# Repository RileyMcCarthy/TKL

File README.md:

# TKL
Custom 10 keyless keyboard PCB and case.

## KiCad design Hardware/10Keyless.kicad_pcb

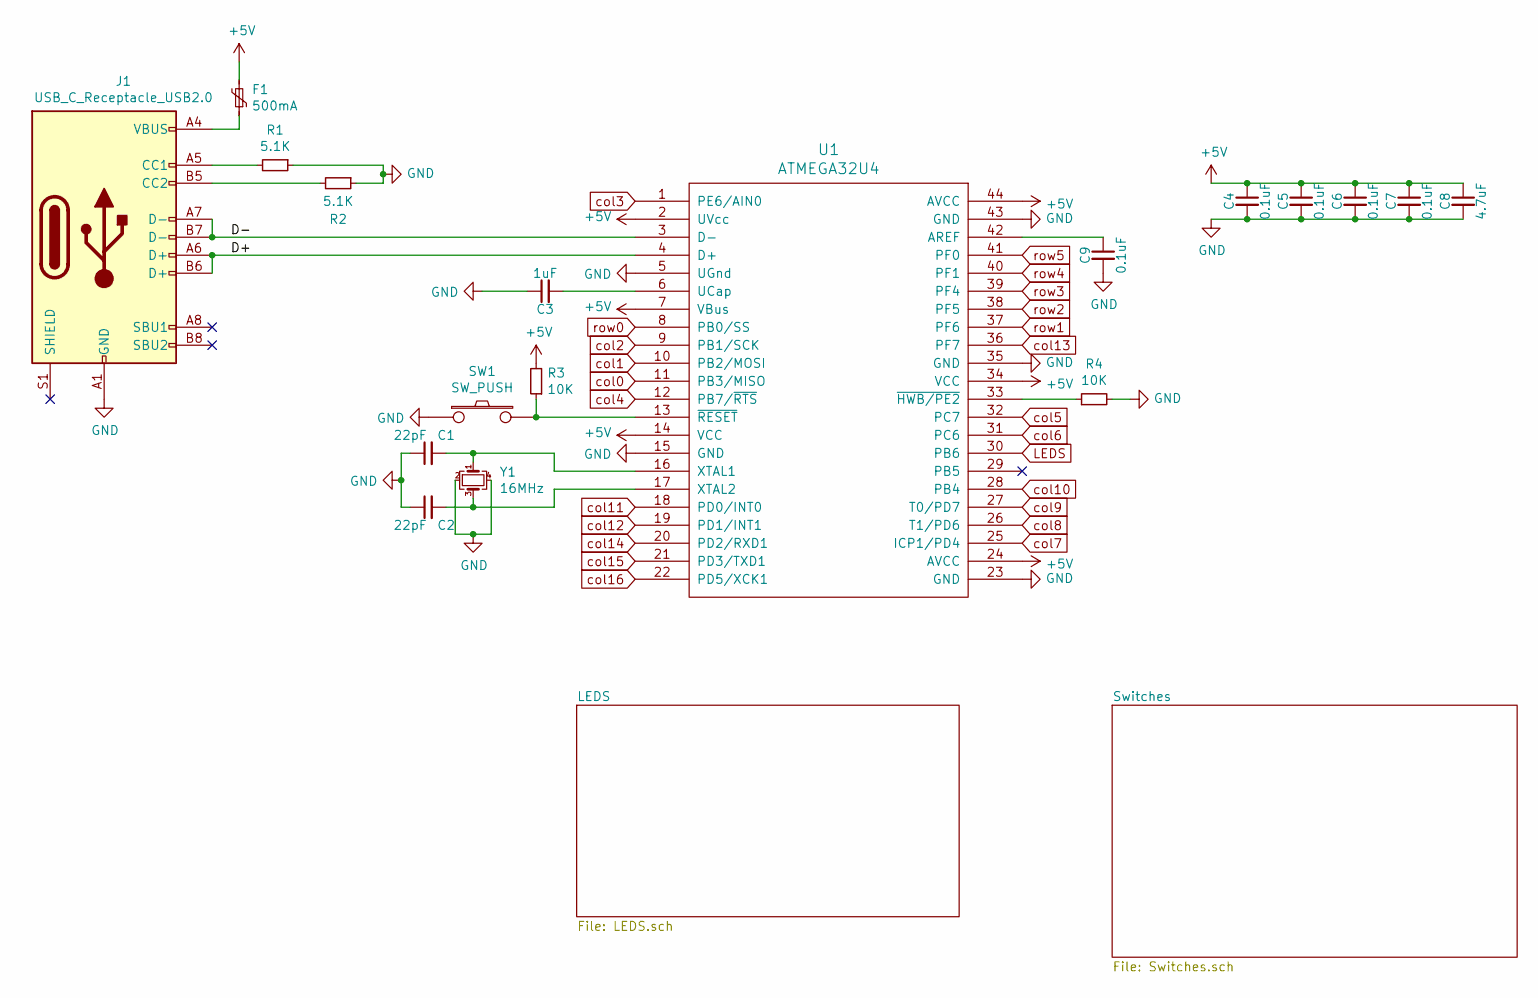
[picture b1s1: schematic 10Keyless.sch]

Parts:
C1, C2: 22pF; C_0603_1608Metric_Pad1.08x0.95mm_HandSolder; LCSC C1653
C3: 1uF; C_0603_1608Metric_Pad1.08x0.95mm_HandSolder; LCSC C15849
C4, C5, C6, C7, C9: 0.1uF; C_0603_1608Metric_Pad1.08x0.95mm_HandSolder; LCSC C14663
C8: 4.7uF; C_0603_1608Metric_Pad1.08x0.95mm_HandSolder; LCSC C19666
F1: 500mA; Fuse_0603_1608Metric_Pad1.05x0.95mm_HandSolder
J1: USB_C_Receptacle_USB2.0; USB_C_Receptacle_Palconn_UTC16-G; LCSC C223907
R1, R2: 5.1K; R_0603_1608Metric; LCSC C23186
R3, R4: 10K; R_0603_1608Metric; LCSC C25804
SW1: SW_PUSH; SW_Push_1P1T_NO_6x6mm_H9.5mm
U1: ATMEGA32U4; LQFP-44_10x10mm_P0.8mm; LCSC C44854
Y1: 16MHz; Crystal_SMD_3225-4Pin_3.2x2.5mm_HandSoldering; LCSC C389842

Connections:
+5V: C4.1, C5.1, C6.1, C7.1, C8.1, F1.2, R3.2, U1.2 (UVcc), U1.7 (VBus), U1.14 (VCC), U1.24 (AVCC), U1.34 (VCC), U1.44 (AVCC); also elsewhere on the board
/D+: J1.A6 (D+), J1.B6 (D+), U1.4 (D+)
/D-: J1.A7 (D-), J1.B7 (D-), U1.3 (D-)
GND: C1.1, C2.1, C3.1, C4.2, C5.2, C6.2, C7.2, C8.2, C9.2, J1.A1 (GND), J1.A12 (GND), J1.B1 (GND), J1.B12 (GND), R1.1, R2.1, R4.2, SW1.1, U1.5 (UGnd), U1.15 (GND), U1.23 (GND), U1.35 (GND), U1.43 (GND), Y1.2, Y1.4; also elsewhere on the board
LEDS: U1.30 (PB6); also elsewhere on the board
unnamed: C1.2, U1.16 (XTAL1), Y1.1
unnamed: C2.2, U1.17 (XTAL2), Y1.3
unnamed: C3.2, U1.6 (UCap)
unnamed: C9.1, U1.42 (AREF)
unnamed: F1.1, J1.A4 (VBUS), J1.A9 (VBUS), J1.B4 (VBUS), J1.B9 (VBUS)
unnamed: J1.A5 (CC1), R1.2
unnamed: J1.B5 (CC2), R2.2
unnamed: R3.1, SW1.2, U1.13 (~RESET)
unnamed: R4.1, U1.33 (~HWB/PE2)
col0: U1.11 (PB3/MISO); also elsewhere on the board
col1: U1.10 (PB2/MOSI); also elsewhere on the board
col2: U1.9 (PB1/SCK); also elsewhere on the board
col3: U1.1 (PE6/AIN0); also elsewhere on the board
col4: U1.12 (PB7/~RTS); also elsewhere on the board
col5: U1.32 (PC7); also elsewhere on the board
col6: U1.31 (PC6); also elsewhere on the board
col7: U1.25 (ICP1/PD4); also elsewhere on the board
col8: U1.26 (T1/PD6); also elsewhere on the board
col9: U1.27 (T0/PD7); also elsewhere on the board
col10: U1.28 (PB4); also elsewhere on the board
col11: U1.18 (PD0/INT0); also elsewhere on the board
col12: U1.19 (PD1/INT1); also elsewhere on the board
col13: U1.36 (PF7); also elsewhere on the board
col14: U1.20 (PD2/RXD1); also elsewhere on the board
col15: U1.21 (PD3/TXD1); also elsewhere on the board
col16: U1.22 (PD5/XCK1); also elsewhere on the board
row0: U1.8 (PB0/SS); also elsewhere on the board
row1: U1.37 (PF6); also elsewhere on the board
row2: U1.38 (PF5); also elsewhere on the board
row3: U1.39 (PF4); also elsewhere on the board
row4: U1.40 (PF1); also elsewhere on the board
row5: U1.41 (PF0); also elsewhere on the board

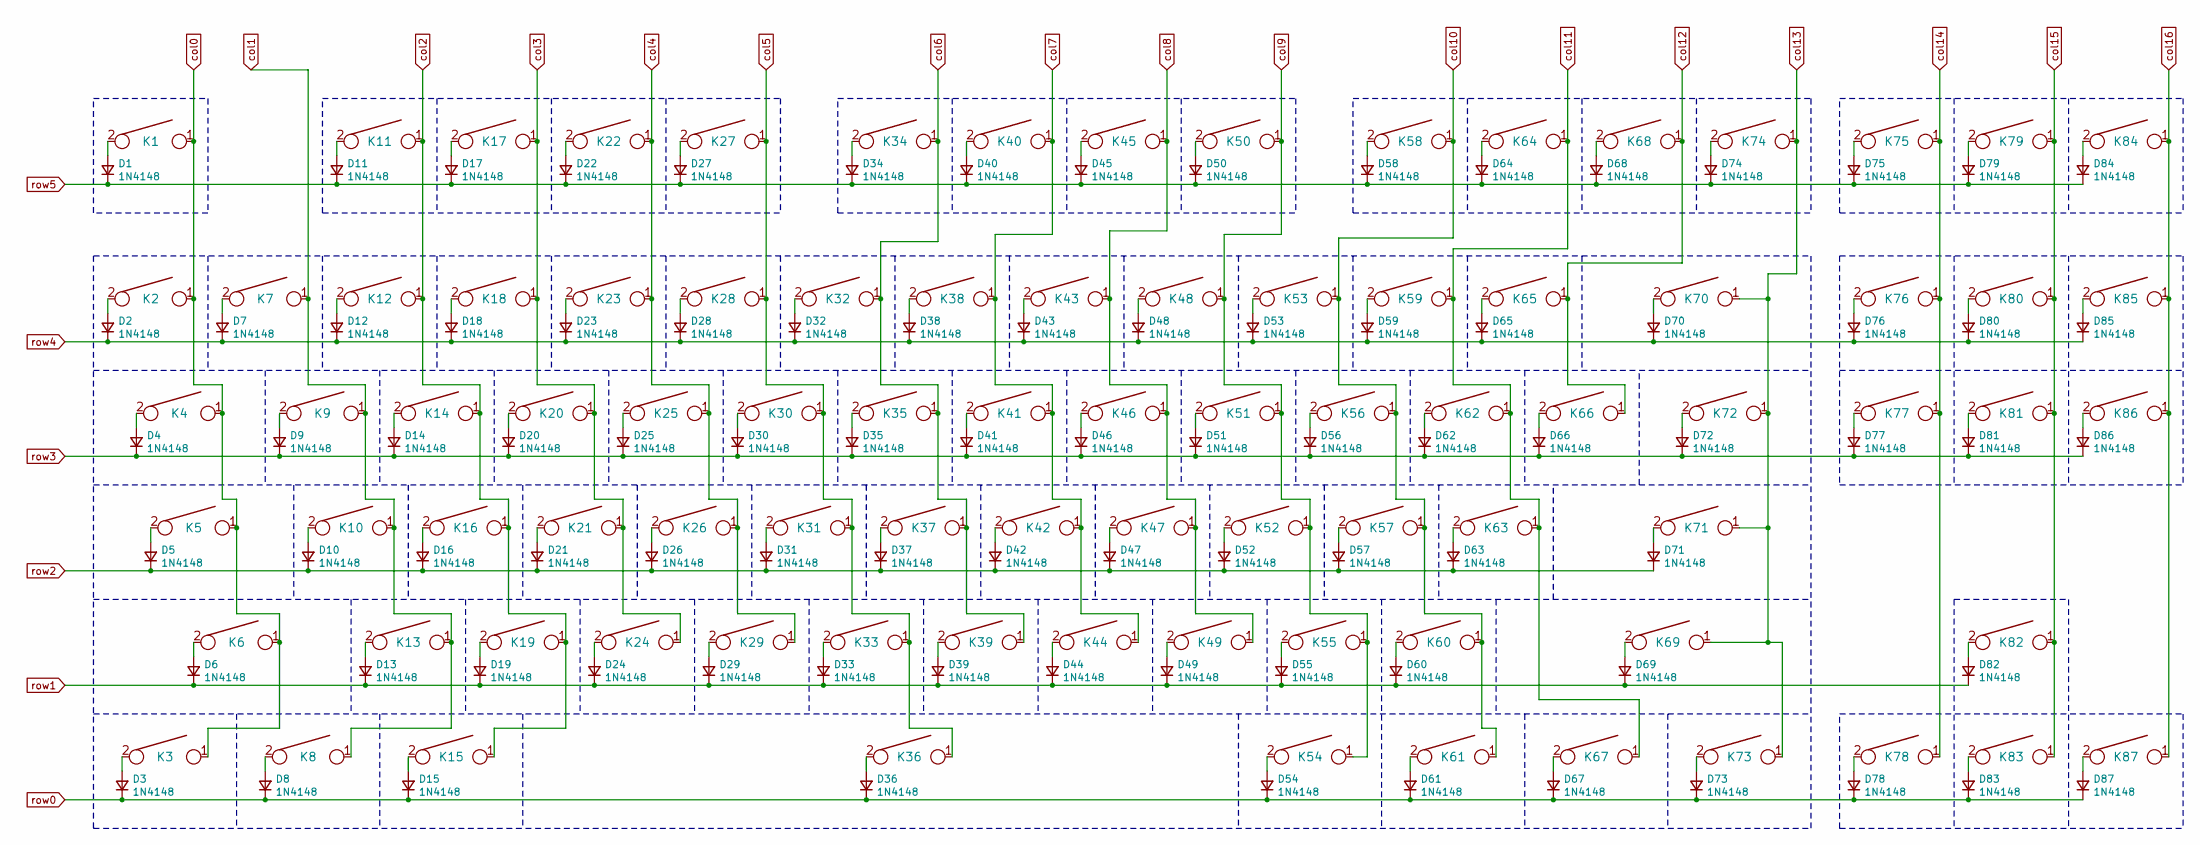
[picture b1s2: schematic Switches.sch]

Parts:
D1, D2, D3, D4, D5, D6, D7, D8, D9, D10, D11, D12, D13, D14, D15, D16, D17, D18, D19, D20, D21, D22, D23, D24, D25, D26, D27, D28, D29, D30, D31, D32, D33, D34, D35, D36, D37, D38, D39, D40, D41, D42, D43, D44, D45, D46, D47, D48, D49, D50, D51, D52, D53, D54, D55, D56, D57, D58, D59, D60, D61, D62, D63, D64, D65, D66, D67, D68, D69, D70, D71, D72, D73, D74, D75, D76, D77, D78, D79, D80, D81, D82, D83, D84, D85, D86, D87: 1N4148; D_SOD-123; LCSC C81598
K1: ESC; SW_Cherry_MX_1.00u_PCB
K2: tilda; SW_Cherry_MX_1.00u_PCB
K3: ctrl; SW_Cherry_MX_1.25u_PCB
K4: tab; SW_Cherry_MX_1.50u_PCB
K5: caps; SW_Cherry_MX_1.75u_PCB
K6: shift; SW_Cherry_MX_2.25u_PCB
K7: 1; SW_Cherry_MX_1.00u_PCB
K8: win; SW_Cherry_MX_1.25u_PCB
K9: q; SW_Cherry_MX_1.00u_PCB
K10: a; SW_Cherry_MX_1.00u_PCB
K11: F1; SW_Cherry_MX_1.00u_PCB
K12: 2; SW_Cherry_MX_1.00u_PCB
K13: z; SW_Cherry_MX_1.00u_PCB
K14: w; SW_Cherry_MX_1.00u_PCB
K15: alt; SW_Cherry_MX_1.25u_PCB
K16: s; SW_Cherry_MX_1.00u_PCB
K17: F2; SW_Cherry_MX_1.00u_PCB
K18: 3; SW_Cherry_MX_1.00u_PCB
K19: x; SW_Cherry_MX_1.00u_PCB
K20: e; SW_Cherry_MX_1.00u_PCB
K21: d; SW_Cherry_MX_1.00u_PCB
K22: F3; SW_Cherry_MX_1.00u_PCB
K23: 4; SW_Cherry_MX_1.00u_PCB
K24: c; SW_Cherry_MX_1.00u_PCB
K25: r; SW_Cherry_MX_1.00u_PCB
K26: f; SW_Cherry_MX_1.00u_PCB
K27: F4; SW_Cherry_MX_1.00u_PCB
K28: 5; SW_Cherry_MX_1.00u_PCB
K29: v; SW_Cherry_MX_1.00u_PCB
K30: t; SW_Cherry_MX_1.00u_PCB
K31: g; SW_Cherry_MX_1.00u_PCB
K32: 6; SW_Cherry_MX_1.00u_PCB
K33: b; SW_Cherry_MX_1.00u_PCB
K34: F5; SW_Cherry_MX_1.00u_PCB
K35: y; SW_Cherry_MX_1.00u_PCB
K36: space; SW_Cherry_MX_6.25u_PCB
K37: h; SW_Cherry_MX_1.00u_PCB
K38: 7; SW_Cherry_MX_1.00u_PCB
K39: n; SW_Cherry_MX_1.00u_PCB
K40: F6; SW_Cherry_MX_1.00u_PCB
K41: u; SW_Cherry_MX_1.00u_PCB
K42: j; SW_Cherry_MX_1.00u_PCB
K43: 8; SW_Cherry_MX_1.00u_PCB
K44: m; SW_Cherry_MX_1.00u_PCB
K45: F7; SW_Cherry_MX_1.00u_PCB
K46: i; SW_Cherry_MX_1.00u_PCB
K47: k; SW_Cherry_MX_1.00u_PCB
K48: 9; SW_Cherry_MX_1.00u_PCB
K49: comma; SW_Cherry_MX_1.00u_PCB
K50: F8; SW_Cherry_MX_1.00u_PCB
K51: o; SW_Cherry_MX_1.00u_PCB
K52: l; SW_Cherry_MX_1.00u_PCB
K53: 0; SW_Cherry_MX_1.00u_PCB
K54: alt1; SW_Cherry_MX_1.25u_PCB
K55: period; SW_Cherry_MX_1.00u_PCB
K56: p; SW_Cherry_MX_1.00u_PCB
K57: semicolon; SW_Cherry_MX_1.00u_PCB
K58: F9; SW_Cherry_MX_1.00u_PCB
K59: minus; SW_Cherry_MX_1.00u_PCB
K60: slash; SW_Cherry_MX_1.00u_PCB
K61: win1; SW_Cherry_MX_1.25u_PCB
K62: open_bracket; SW_Cherry_MX_1.00u_PCB
K63: quote; SW_Cherry_MX_1.00u_PCB
K64: F10; SW_Cherry_MX_1.00u_PCB
K65: plus; SW_Cherry_MX_1.00u_PCB
K66: closed_bracket; SW_Cherry_MX_1.00u_PCB
K67: menu; SW_Cherry_MX_1.25u_PCB
K68: F11; SW_Cherry_MX_1.00u_PCB
K69: shift1; SW_Cherry_MX_2.75u_PCB
K70: backspace; SW_Cherry_MX_2.00u_PCB
K71: enter; SW_Cherry_MX_2.25u_PCB
K72: bslash; SW_Cherry_MX_1.50u_PCB
K73: ctrl1; SW_Cherry_MX_1.25u_PCB
K74: F12; SW_Cherry_MX_1.00u_PCB
K75: prtSc; SW_Cherry_MX_1.00u_PCB
K76: insert; SW_Cherry_MX_1.00u_PCB
K77: del; SW_Cherry_MX_1.00u_PCB
K78: left; SW_Cherry_MX_1.00u_PCB
K79: scroll_lock; SW_Cherry_MX_1.00u_PCB
K80: home; SW_Cherry_MX_1.00u_PCB
K81: end; SW_Cherry_MX_1.00u_PCB
K82: up; SW_Cherry_MX_1.00u_PCB
K83: down; SW_Cherry_MX_1.00u_PCB
K84: pause; SW_Cherry_MX_1.00u_PCB
K85: pgup; SW_Cherry_MX_1.00u_PCB
K86: pgdn; SW_Cherry_MX_1.00u_PCB
K87: right; SW_Cherry_MX_1.00u_PCB

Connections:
unnamed: D1.2 (A), K1.2
unnamed: D2.2 (A), K2.2
unnamed: D3.2 (A), K3.2
unnamed: D4.2 (A), K4.2
unnamed: D5.2 (A), K5.2
unnamed: D6.2 (A), K6.2
unnamed: D7.2 (A), K7.2
unnamed: D8.2 (A), K8.2
unnamed: D9.2 (A), K9.2
unnamed: D10.2 (A), K10.2
unnamed: D11.2 (A), K11.2
unnamed: D12.2 (A), K12.2
unnamed: D13.2 (A), K13.2
unnamed: D14.2 (A), K14.2
unnamed: D15.2 (A), K15.2
unnamed: D16.2 (A), K16.2
unnamed: D17.2 (A), K17.2
unnamed: D18.2 (A), K18.2
unnamed: D19.2 (A), K19.2
unnamed: D20.2 (A), K20.2
unnamed: D21.2 (A), K21.2
unnamed: D22.2 (A), K22.2
unnamed: D23.2 (A), K23.2
unnamed: D24.2 (A), K24.2
unnamed: D25.2 (A), K25.2
unnamed: D26.2 (A), K26.2
unnamed: D27.2 (A), K27.2
unnamed: D28.2 (A), K28.2
unnamed: D29.2 (A), K29.2
unnamed: D30.2 (A), K30.2
unnamed: D31.2 (A), K31.2
unnamed: D32.2 (A), K32.2
unnamed: D33.2 (A), K33.2
unnamed: D34.2 (A), K34.2
unnamed: D35.2 (A), K35.2
unnamed: D36.2 (A), K36.2
unnamed: D37.2 (A), K37.2
unnamed: D38.2 (A), K38.2
unnamed: D39.2 (A), K39.2
unnamed: D40.2 (A), K40.2
unnamed: D41.2 (A), K41.2
unnamed: D42.2 (A), K42.2
unnamed: D43.2 (A), K43.2
unnamed: D44.2 (A), K44.2
unnamed: D45.2 (A), K45.2
unnamed: D46.2 (A), K46.2
unnamed: D47.2 (A), K47.2
unnamed: D48.2 (A), K48.2
unnamed: D49.2 (A), K49.2
unnamed: D50.2 (A), K50.2
unnamed: D51.2 (A), K51.2
unnamed: D52.2 (A), K52.2
unnamed: D53.2 (A), K53.2
unnamed: D54.2 (A), K54.2
unnamed: D55.2 (A), K55.2
unnamed: D56.2 (A), K56.2
unnamed: D57.2 (A), K57.2
unnamed: D58.2 (A), K58.2
unnamed: D59.2 (A), K59.2
unnamed: D60.2 (A), K60.2
unnamed: D61.2 (A), K61.2
unnamed: D62.2 (A), K62.2
unnamed: D63.2 (A), K63.2
unnamed: D64.2 (A), K64.2
unnamed: D65.2 (A), K65.2
unnamed: D66.2 (A), K66.2
unnamed: D67.2 (A), K67.2
unnamed: D68.2 (A), K68.2
unnamed: D69.2 (A), K69.2
unnamed: D70.2 (A), K70.2
unnamed: D71.2 (A), K71.2
unnamed: D72.2 (A), K72.2
unnamed: D73.2 (A), K73.2
unnamed: D74.2 (A), K74.2
unnamed: D75.2 (A), K75.2
unnamed: D76.2 (A), K76.2
unnamed: D77.2 (A), K77.2
unnamed: D78.2 (A), K78.2
unnamed: D79.2 (A), K79.2
unnamed: D80.2 (A), K80.2
unnamed: D81.2 (A), K81.2
unnamed: D82.2 (A), K82.2
unnamed: D83.2 (A), K83.2
unnamed: D84.2 (A), K84.2
unnamed: D85.2 (A), K85.2
unnamed: D86.2 (A), K86.2
unnamed: D87.2 (A), K87.2
col0: K1.1, K2.1, K3.1, K4.1, K5.1, K6.1; also elsewhere on the board
col1: K7.1, K8.1, K9.1, K10.1, K13.1; also elsewhere on the board
col2: K11.1, K12.1, K14.1, K15.1, K16.1, K19.1; also elsewhere on the board
col3: K17.1, K18.1, K20.1, K21.1, K24.1; also elsewhere on the board
col4: K22.1, K23.1, K25.1, K26.1, K29.1; also elsewhere on the board
col5: K27.1, K28.1, K30.1, K31.1, K33.1, K36.1; also elsewhere on the board
col6: K32.1, K34.1, K35.1, K37.1, K39.1; also elsewhere on the board
col7: K38.1, K40.1, K41.1, K42.1, K44.1; also elsewhere on the board
col8: K43.1, K45.1, K46.1, K47.1, K49.1; also elsewhere on the board
col9: K48.1, K50.1, K51.1, K52.1, K54.1, K55.1; also elsewhere on the board
col10: K53.1, K56.1, K57.1, K58.1, K60.1, K61.1; also elsewhere on the board
col11: K59.1, K62.1, K63.1, K64.1, K67.1; also elsewhere on the board
col12: K65.1, K66.1, K68.1; also elsewhere on the board
col13: K69.1, K70.1, K71.1, K72.1, K73.1, K74.1; also elsewhere on the board
col14: K75.1, K76.1, K77.1, K78.1; also elsewhere on the board
col15: K79.1, K80.1, K81.1, K82.1, K83.1; also elsewhere on the board
col16: K84.1, K85.1, K86.1, K87.1; also elsewhere on the board
row0: D3.1 (K), D8.1 (K), D15.1 (K), D36.1 (K), D54.1 (K), D61.1 (K), D67.1 (K), D73.1 (K), D78.1 (K), D83.1 (K), D87.1 (K); also elsewhere on the board
row1: D6.1 (K), D13.1 (K), D19.1 (K), D24.1 (K), D29.1 (K), D33.1 (K), D39.1 (K), D44.1 (K), D49.1 (K), D55.1 (K), D60.1 (K), D69.1 (K), D82.1 (K); also elsewhere on the board
row2: D5.1 (K), D10.1 (K), D16.1 (K), D21.1 (K), D26.1 (K), D31.1 (K), D37.1 (K), D42.1 (K), D47.1 (K), D52.1 (K), D57.1 (K), D63.1 (K), D71.1 (K); also elsewhere on the board
row3: D4.1 (K), D9.1 (K), D14.1 (K), D20.1 (K), D25.1 (K), D30.1 (K), D35.1 (K), D41.1 (K), D46.1 (K), D51.1 (K), D56.1 (K), D62.1 (K), D66.1 (K), D72.1 (K), D77.1 (K), D81.1 (K), D86.1 (K); also elsewhere on the board
row4: D2.1 (K), D7.1 (K), D12.1 (K), D18.1 (K), D23.1 (K), D28.1 (K), D32.1 (K), D38.1 (K), D43.1 (K), D48.1 (K), D53.1 (K), D59.1 (K), D65.1 (K), D70.1 (K), D76.1 (K), D80.1 (K), D85.1 (K); also elsewhere on the board
row5: D1.1 (K), D11.1 (K), D17.1 (K), D22.1 (K), D27.1 (K), D34.1 (K), D40.1 (K), D45.1 (K), D50.1 (K), D58.1 (K), D64.1 (K), D68.1 (K), D74.1 (K), D75.1 (K), D79.1 (K), D84.1 (K); also elsewhere on the board

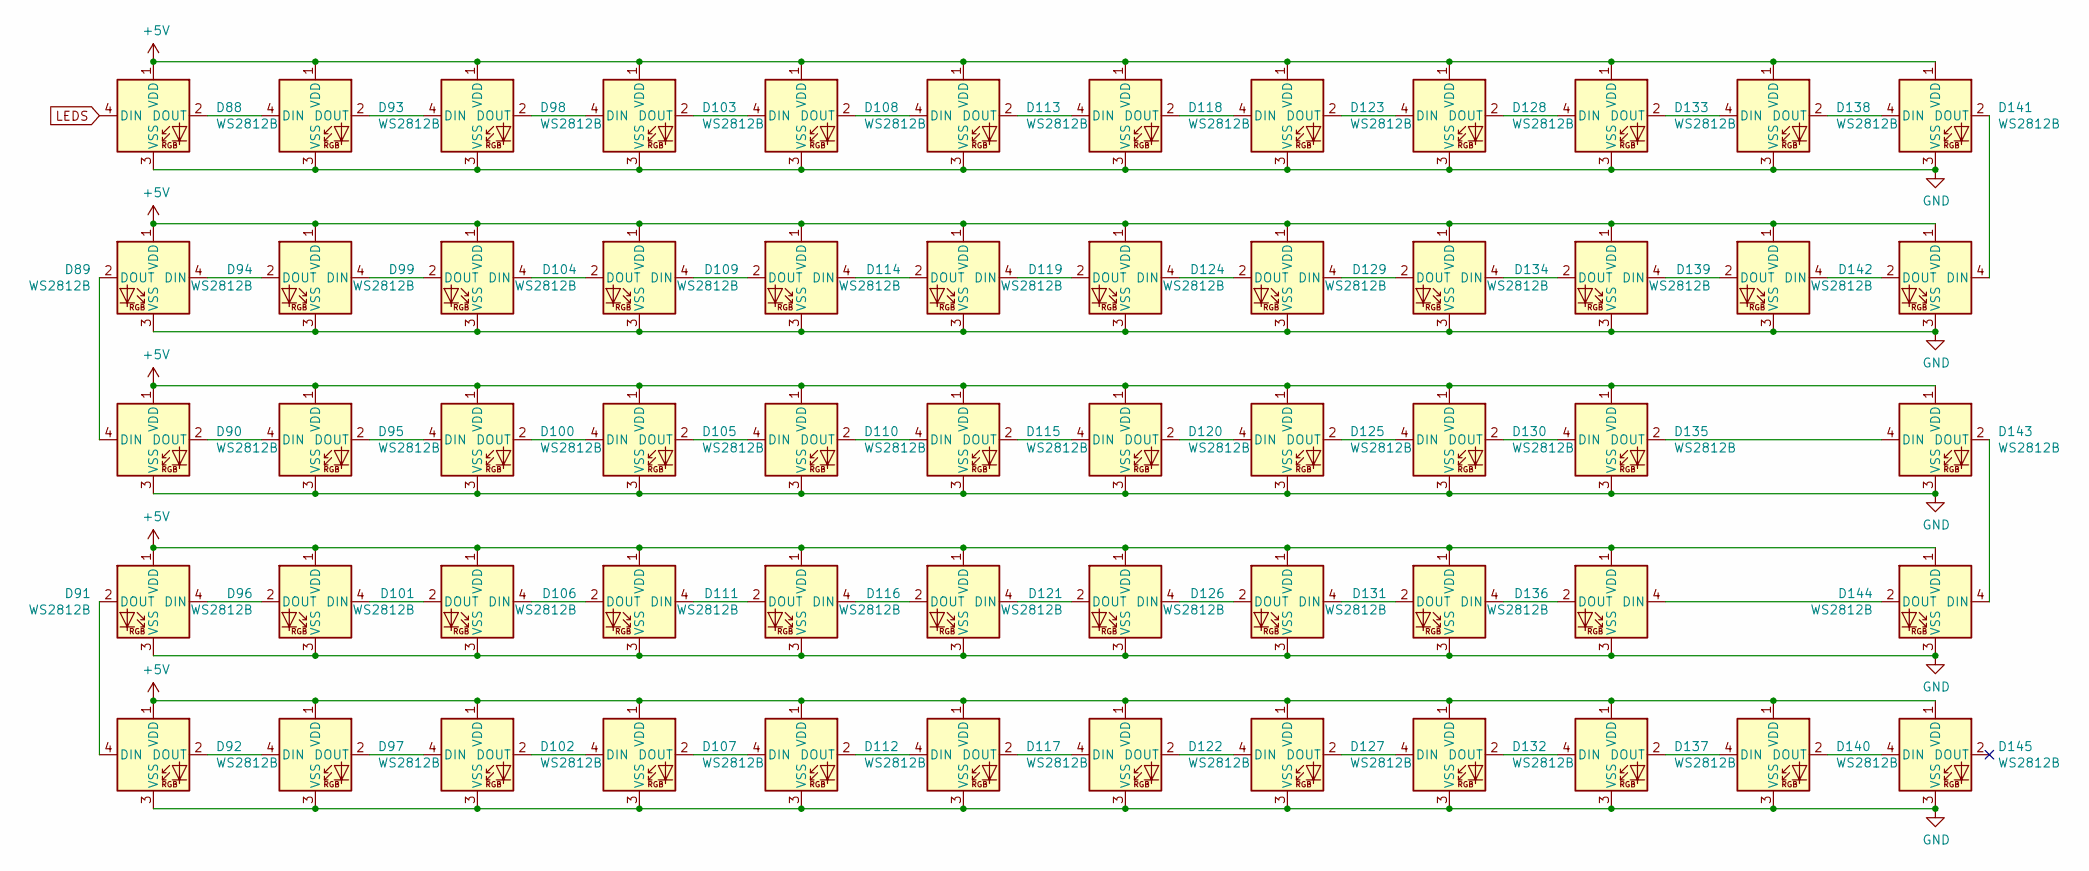
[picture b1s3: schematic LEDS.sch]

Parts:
D88, D89, D90, D91, D92, D93, D94, D95, D96, D97, D98, D99, D100, D101, D102, D103, D104, D105, D106, D107, D108, D109, D110, D111, D112, D113, D114, D115, D116, D117, D118, D119, D120, D121, D122, D123, D124, D125, D126, D127, D128, D129, D130, D131, D132, D133, D134, D135, D136, D137, D138, D139, D140, D141, D142, D143, D144, D145: WS2812B; LED_WS2812B_PLCC4_5.0x5.0mm_P3.2mm; LCSC C114587

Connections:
+5V: D88.1 (VDD), D89.1 (VDD), D90.1 (VDD), D91.1 (VDD), D92.1 (VDD), D93.1 (VDD), D94.1 (VDD), D95.1 (VDD), D96.1 (VDD), D97.1 (VDD), D98.1 (VDD), D99.1 (VDD), D100.1 (VDD), D101.1 (VDD), D102.1 (VDD), D103.1 (VDD), D104.1 (VDD), D105.1 (VDD), D106.1 (VDD), D107.1 (VDD), D108.1 (VDD), D109.1 (VDD), D110.1 (VDD), D111.1 (VDD), D112.1 (VDD), D113.1 (VDD), D114.1 (VDD), D115.1 (VDD), D116.1 (VDD), D117.1 (VDD), D118.1 (VDD), D119.1 (VDD), D120.1 (VDD), D121.1 (VDD), D122.1 (VDD), D123.1 (VDD), D124.1 (VDD), D125.1 (VDD), D126.1 (VDD), D127.1 (VDD), D128.1 (VDD), D129.1 (VDD), D130.1 (VDD), D131.1 (VDD), D132.1 (VDD), D133.1 (VDD), D134.1 (VDD), D135.1 (VDD), D136.1 (VDD), D137.1 (VDD), D138.1 (VDD), D139.1 (VDD), D140.1 (VDD), D141.1 (VDD), D142.1 (VDD), D143.1 (VDD), D144.1 (VDD), D145.1 (VDD); also elsewhere on the board
GND: D88.3 (VSS), D89.3 (VSS), D90.3 (VSS), D91.3 (VSS), D92.3 (VSS), D93.3 (VSS), D94.3 (VSS), D95.3 (VSS), D96.3 (VSS), D97.3 (VSS), D98.3 (VSS), D99.3 (VSS), D100.3 (VSS), D101.3 (VSS), D102.3 (VSS), D103.3 (VSS), D104.3 (VSS), D105.3 (VSS), D106.3 (VSS), D107.3 (VSS), D108.3 (VSS), D109.3 (VSS), D110.3 (VSS), D111.3 (VSS), D112.3 (VSS), D113.3 (VSS), D114.3 (VSS), D115.3 (VSS), D116.3 (VSS), D117.3 (VSS), D118.3 (VSS), D119.3 (VSS), D120.3 (VSS), D121.3 (VSS), D122.3 (VSS), D123.3 (VSS), D124.3 (VSS), D125.3 (VSS), D126.3 (VSS), D127.3 (VSS), D128.3 (VSS), D129.3 (VSS), D130.3 (VSS), D131.3 (VSS), D132.3 (VSS), D133.3 (VSS), D134.3 (VSS), D135.3 (VSS), D136.3 (VSS), D137.3 (VSS), D138.3 (VSS), D139.3 (VSS), D140.3 (VSS), D141.3 (VSS), D142.3 (VSS), D143.3 (VSS), D144.3 (VSS), D145.3 (VSS); also elsewhere on the board
LEDS: D88.4 (DIN); also elsewhere on the board
unnamed: D88.2 (DOUT), D93.4 (DIN)
unnamed: D89.2 (DOUT), D90.4 (DIN)
unnamed: D89.4 (DIN), D94.2 (DOUT)
unnamed: D90.2 (DOUT), D95.4 (DIN)
unnamed: D91.2 (DOUT), D92.4 (DIN)
unnamed: D91.4 (DIN), D96.2 (DOUT)
unnamed: D92.2 (DOUT), D97.4 (DIN)
unnamed: D93.2 (DOUT), D98.4 (DIN)
unnamed: D94.4 (DIN), D99.2 (DOUT)
unnamed: D100.2 (DOUT), D105.4 (DIN)
unnamed: D95.2 (DOUT), D100.4 (DIN)
unnamed: D96.4 (DIN), D101.2 (DOUT)
unnamed: D101.4 (DIN), D106.2 (DOUT)
unnamed: D102.2 (DOUT), D107.4 (DIN)
unnamed: D97.2 (DOUT), D102.4 (DIN)
unnamed: D103.2 (DOUT), D108.4 (DIN)
unnamed: D98.2 (DOUT), D103.4 (DIN)
unnamed: D99.4 (DIN), D104.2 (DOUT)
unnamed: D104.4 (DIN), D109.2 (DOUT)
unnamed: D105.2 (DOUT), D110.4 (DIN)
unnamed: D106.4 (DIN), D111.2 (DOUT)
unnamed: D107.2 (DOUT), D112.4 (DIN)
unnamed: D108.2 (DOUT), D113.4 (DIN)
unnamed: D109.4 (DIN), D114.2 (DOUT)
unnamed: D110.2 (DOUT), D115.4 (DIN)
unnamed: D111.4 (DIN), D116.2 (DOUT)
unnamed: D112.2 (DOUT), D117.4 (DIN)
unnamed: D113.2 (DOUT), D118.4 (DIN)
unnamed: D114.4 (DIN), D119.2 (DOUT)
unnamed: D115.2 (DOUT), D120.4 (DIN)
unnamed: D116.4 (DIN), D121.2 (DOUT)
unnamed: D117.2 (DOUT), D122.4 (DIN)
unnamed: D118.2 (DOUT), D123.4 (DIN)
unnamed: D119.4 (DIN), D124.2 (DOUT)
unnamed: D120.2 (DOUT), D125.4 (DIN)
unnamed: D121.4 (DIN), D126.2 (DOUT)
unnamed: D122.2 (DOUT), D127.4 (DIN)
unnamed: D123.2 (DOUT), D128.4 (DIN)
unnamed: D124.4 (DIN), D129.2 (DOUT)
unnamed: D125.2 (DOUT), D130.4 (DIN)
unnamed: D126.4 (DIN), D131.2 (DOUT)
unnamed: D127.2 (DOUT), D132.4 (DIN)
unnamed: D128.2 (DOUT), D133.4 (DIN)
unnamed: D129.4 (DIN), D134.2 (DOUT)
unnamed: D130.2 (DOUT), D135.4 (DIN)
unnamed: D131.4 (DIN), D136.2 (DOUT)
unnamed: D132.2 (DOUT), D137.4 (DIN)
unnamed: D133.2 (DOUT), D138.4 (DIN)
unnamed: D134.4 (DIN), D139.2 (DOUT)
unnamed: D135.2 (DOUT), D143.4 (DIN)
unnamed: D136.4 (DIN), D144.2 (DOUT)
unnamed: D137.2 (DOUT), D140.4 (DIN)
unnamed: D138.2 (DOUT), D141.4 (DIN)
unnamed: D139.4 (DIN), D142.2 (DOUT)
unnamed: D140.2 (DOUT), D145.4 (DIN)
unnamed: D141.2 (DOUT), D142.4 (DIN)
unnamed: D143.2 (DOUT), D144.4 (DIN)

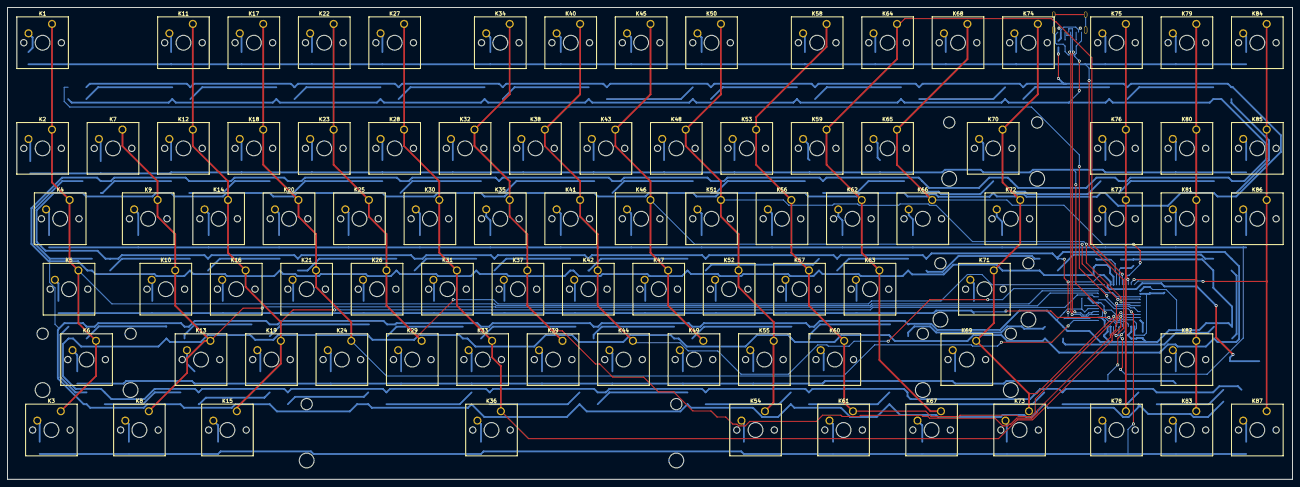
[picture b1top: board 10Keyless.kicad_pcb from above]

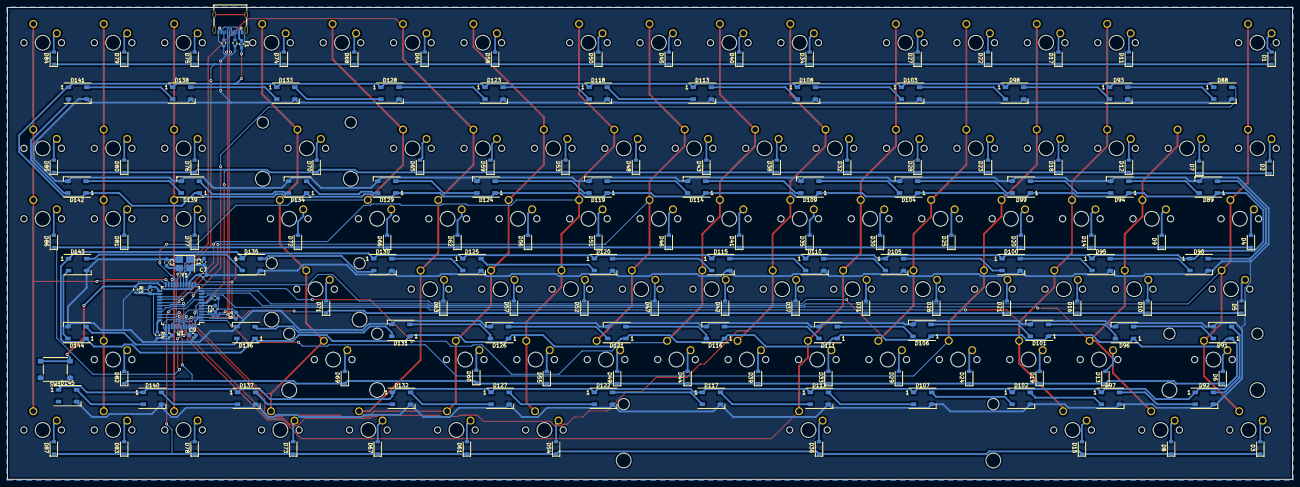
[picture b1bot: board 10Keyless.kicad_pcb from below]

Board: 2 copper layers, 347.6 x 127.6 mm, 250 parts (163 on the bottom side), 181 nets.

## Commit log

2021-05-12 added missing files
